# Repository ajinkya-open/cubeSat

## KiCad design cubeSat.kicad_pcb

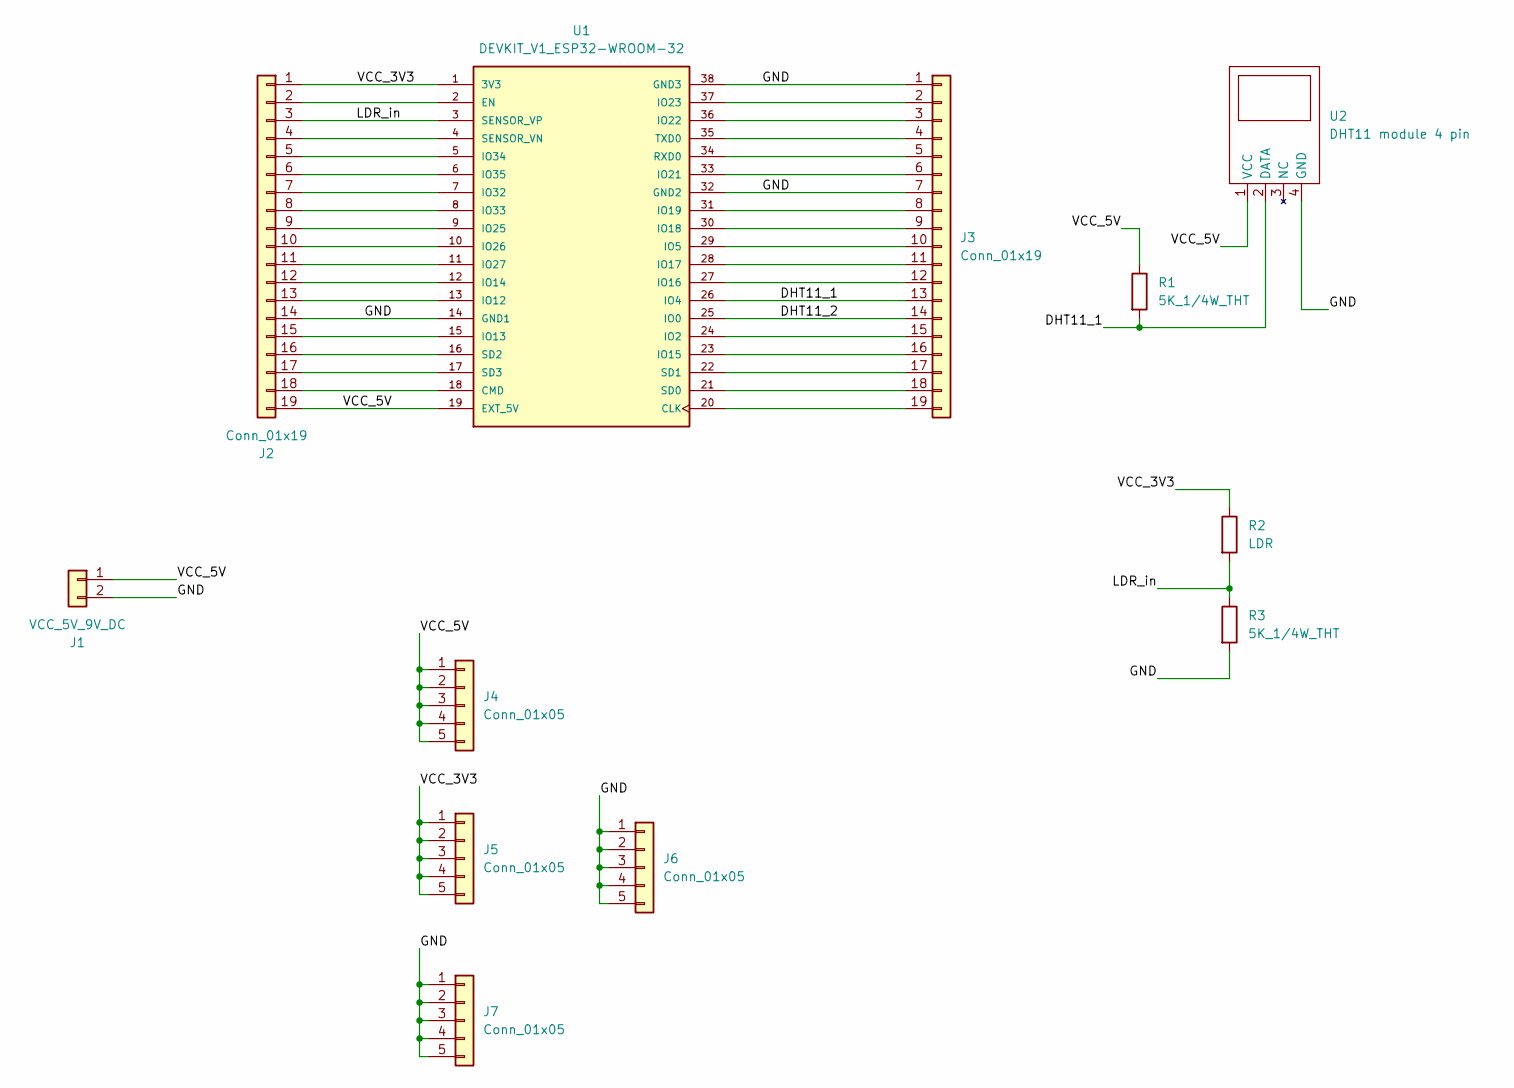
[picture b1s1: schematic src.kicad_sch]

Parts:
J1: VCC_5V_9V_DC; JST_XH_S2B-XH-A_1x02_P2.50mm_Horizontal
J2, J3: Conn_01x19; PinSocket_1x19_P2.54mm_Vertical
J4, J5, J6, J7: Conn_01x05; PinSocket_1x05_P2.54mm_Vertical
R1, R3: 5K_1/4W_THT; R_Axial_DIN0207_L6.3mm_D2.5mm_P7.62mm_Horizontal
R2: LDR; R_LDR_5.0x4.1mm_P3mm_Vertical
U1: DEVKIT_V1_ESP32-WROOM-32; MODULE_DEVKIT_V1_ESP32-WROOM-32; PARTREV N/A
U2: DHT11 module 4 pin; PinSocket_1x04_P2.54mm_Vertical

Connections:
/SRC/DHT11_1: J3.13, R1.2, U1.26 (IO4), U2.2 (DATA)
/SRC/DHT11_2: J3.14, U1.25 (IO0)
/SRC/GND: J1.2, J2.14, J3.1, J3.7, J6.1, J6.2, J6.3, J6.4, J6.5, J7.1, J7.2, J7.3, J7.4, J7.5, R3.2, U1.14 (GND1), U1.32 (GND2), U1.38 (GND3), U2.4 (GND)
/SRC/LDR_in: J2.3, R2.2, R3.1, U1.3 (SENSOR_VP)
/SRC/VCC_3V3: J2.1, J5.1, J5.2, J5.3, J5.4, J5.5, R2.1, U1.1 (3V3)
/SRC/VCC_5V: J1.1, J2.19, J4.1, J4.2, J4.3, J4.4, J4.5, R1.1, U1.19 (EXT_5V), U2.1 (VCC)
unnamed: J2.2, U1.2 (EN)
unnamed: J2.4, U1.4 (SENSOR_VN)
unnamed: J2.5, U1.5 (IO34)
unnamed: J2.6, U1.6 (IO35)
unnamed: J2.7, U1.7 (IO32)
unnamed: J2.8, U1.8 (IO33)
unnamed: J2.9, U1.9 (IO25)
unnamed: J2.10, U1.10 (IO26)
unnamed: J2.11, U1.11 (IO27)
unnamed: J2.12, U1.12 (IO14)
unnamed: J2.13, U1.13 (IO12)
unnamed: J2.15, U1.15 (IO13)
unnamed: J2.16, U1.16 (SD2)
unnamed: J2.17, U1.17 (SD3)
unnamed: J2.18, U1.18 (CMD)
unnamed: J3.2, U1.37 (IO23)
unnamed: J3.3, U1.36 (IO22)
unnamed: J3.4, U1.35 (TXD0)
unnamed: J3.5, U1.34 (RXD0)
unnamed: J3.6, U1.33 (IO21)
unnamed: J3.8, U1.31 (IO19)
unnamed: J3.9, U1.30 (IO18)
unnamed: J3.10, U1.29 (IO5)
unnamed: J3.11, U1.28 (IO17)
unnamed: J3.12, U1.27 (IO16)
unnamed: J3.15, U1.24 (IO2)
unnamed: J3.16, U1.23 (IO15)
unnamed: J3.17, U1.22 (SD1)
unnamed: J3.18, U1.21 (SD0)
unnamed: J3.19, U1.20 (CLK)

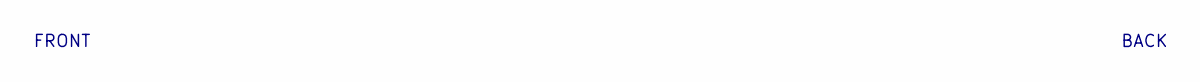
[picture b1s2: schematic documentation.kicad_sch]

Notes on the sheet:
BACK
FRONT

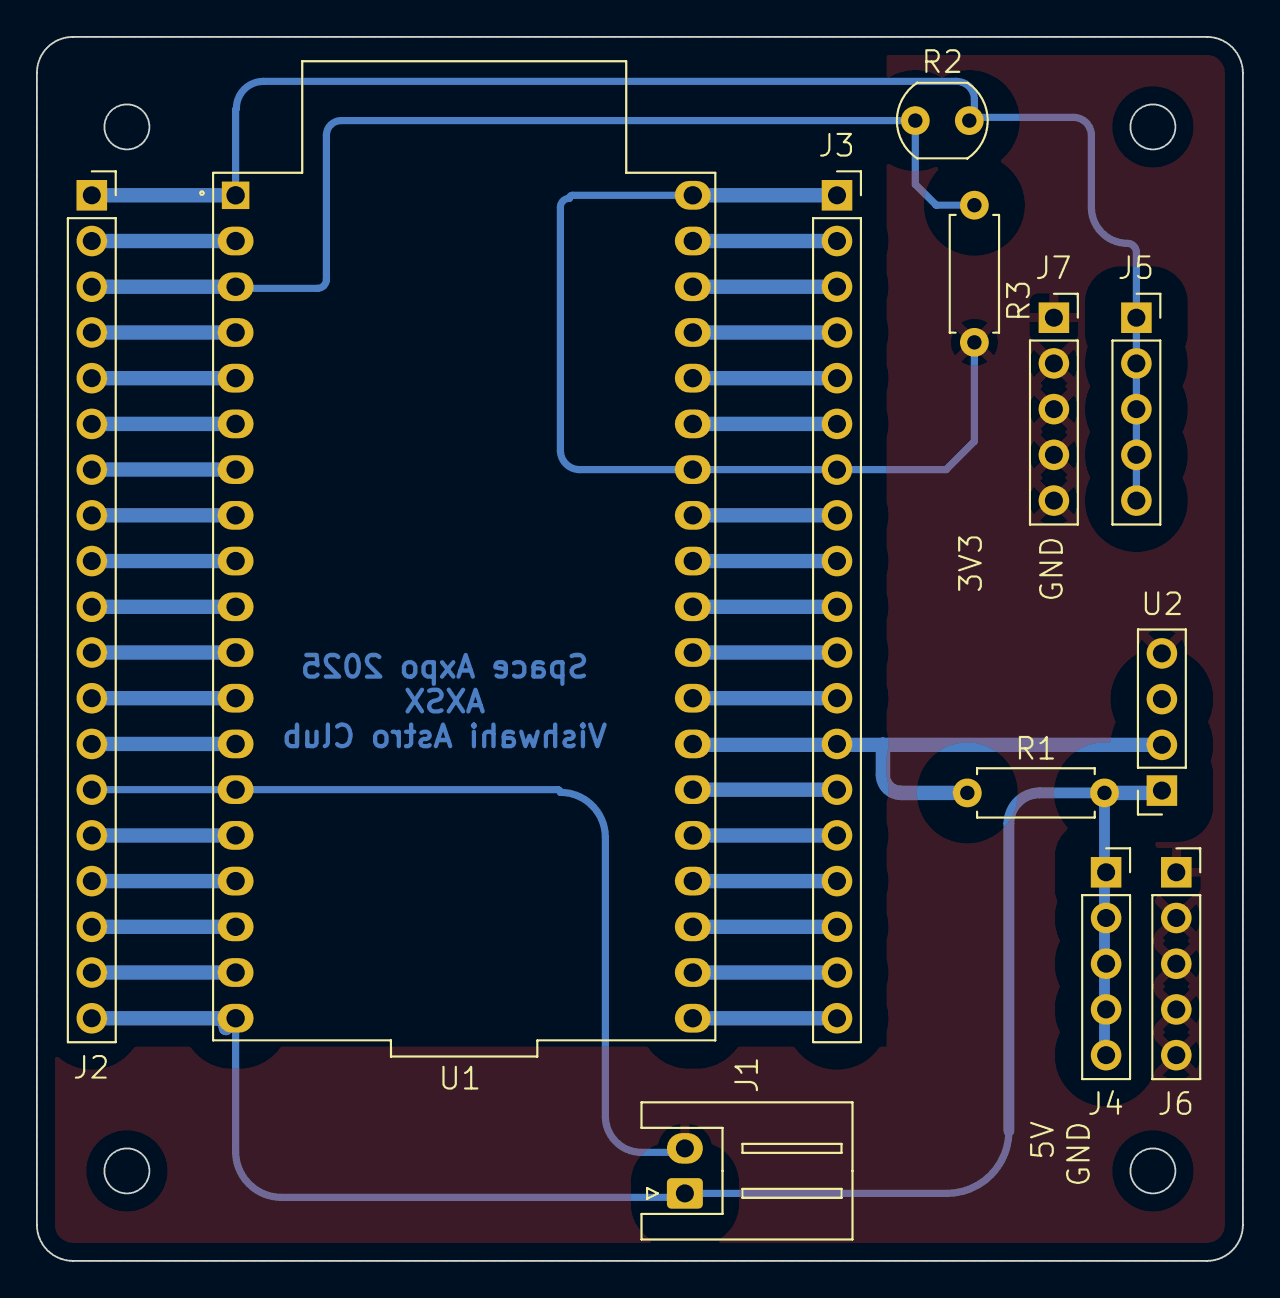
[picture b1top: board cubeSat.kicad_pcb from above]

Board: 2 copper layers, 67.0 x 68.0 mm, 12 parts (0 on the bottom side), 36 nets.

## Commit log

2025-08-28 init
2025-08-28 removed company files
2025-08-28 added Egde cut
2025-08-28 ESP_DHT_added
2025-08-28 added dimensions
2025-08-28 copy_first
2025-08-28 added commnets on pcb with perifferals
2025-08-28 added comments and exported for prod
2025-08-28 increased clearance for pcb manufacturing
